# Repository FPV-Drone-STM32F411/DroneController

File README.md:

# FPV Drone PCB Full PCB + Code + Assembly

**A comprehensive, fully open-source FPV drone platform**: a two-board avionics stack (flight computer + power/ESC) complete with their codebase *and* a lightweight, robust airframe. All KiCad 9.0 design files, firmware, and CAD are included. Media of all PCBs, schematics and airframe are attached within this repository. 

## Overview

This project develops an FPV drone around two custom 5×5 PCBs: a **STM32F411 flight computer** and a **STM32F405 power distribution + ESC board**. esigned for compatibility with **Betaflight** (FC) and **AM32** (ESC). Both are built around the STM32 chipset and designed to be compatible with BetaFlight and AM32 requirements.

**Manufacturing Sponsor:** Huge thanks to **[PCBWay](https://www.pcbway.com/)** for sponsoring fabrication and assembly of the MKII flight computer. Their high-quality manufacturing, quick turnaround, significantly accelerated the build process. Moreover, their service was excellent and addressed questions promptly and clearly. As a bonus, PCBWay offers affordable, unique **silkscreen colours**. PCBWay is highly recommended and proved to be a great fit for the FPV-Drone-STM32F411 project.

**MKII Flight Computer 3D Model**

**What’s new (MKII & Airframe)**
- **MKII Flight Computer:** UART and SWD flash options, cost-efficient and compact IMU (ICM-42605), oscilloscope-friendly SPI test pads, expanded test points, JST connectors, improved routing for debugability.
- **Open-Source Airframe:** integrated landing legs, structural reinforcements, and geometry to accommodate **~935 KV BLDC motors**; CAD provided for easy printing/mods.

## Airframe

The airframe is designed to be **robust and lightweight** with:
- **Integrated landing legs** and **structural reinforcements** for durability  
- Geometry to suit **~935 KV** brushless motors (modeled in CAD)  
- CAD provided for printing and customization

**Printing tips (suggested):**
- Arms/plates: CF-reinforced nylon or strong PLA+/PETG  
- Landing legs: TPU for impact absorption
- Verify clearances for your chosen motor + prop combo (aimed at 5″ class)

## Hardware Details

 **Integrated PCB Design**
  - Flight Controller: STM32F411CEU6 (ARM Cortex M4)
  - Power/ESC Board: High-current paths, AM32 compatible design
    
 **Connectivity**
  - All peripherals utilize SPI for high-speed sensor communication
  - USB-C, JTAG, SWD
  - UART port for external peripheral
  - Backup Coin Cell Battery Port
  - FTDI programming interface

<ins>**Flight Controller Board**</ins>
- STM32F411CEU6 microcontroller
- 12MHz external crystal oscillator
- ICM-42605 gyroscope/accelerometer
- BMP280 barometer for altitude hold
- L86-M33 GPS for postional tracking
- SX 1276 LoRa 915MHz Transciever NiceRF Module
- Power options, USB-C, LDO and External 3.3V Connection

<ins>**Power and ESC Board**</ins>

**Power System**
- SWD Flash
- DC-DC buck converter for efficient power regulation
- Support for 3S-4S LiPo batteries (11.1V-16.8V)
- XT-60 connector for battery input
- Electric Speed Controller for a BLDC motor

**Electronic Speed Controller (ESC)**
- AM32 compatible
- 10A 935 KV motor capability
- Thermal management design

## Software Compatibility

This drone design is compatible with:
- BetaFlight (recommended for racing/freestyle)
- INAV (for GPS functions)
- Ardupilot (for autonomous capabilities)
- AM32 (for ESC functionality)
- STM32CUBEIDE (Coded in C for entire codebase)

### Bill of Materials

| Component | Description | Specification |
|-----------|-------------|---------------|
| Frame | Open-Source CAD | 5″ class geometry w/ landing legs   |
| Motors | Brushless | 935 KV (example: 1800 KV 5″ also viable) |
| Battery | LiPo | 4S 1500mAh 100C (recommended) |
| Propellers | 5-inch | Matched to motor and frame |
| Camera | FPV | CCD or CMOS based on preference |
| Video Transmitter | 5.8GHz | Power output based on needs |
| Receiver | Radio control | Compatible with SX1276 LoRa Transciever |
| LoRa Antenna | 915MHz |SMA compatible quarter-wavelength antenna|

### Electronics Knowledge
- Basic soldering skills
- Understanding of power systems
- Familiarity with microcontrollers
- Ability to flash firmware through CUBEIDE

## Testing Procedures

1. Power system verification (voltage output, regulation)
2. Motor/ESC testing with oscillosocpe
3. SPI testing using oscciloscope test pads
4. Sensor calibration and verification
5. Radio range and failsafe testing
6. Controlled hover tests
7. Full flight testing

# Media
## Most Updated
### Airframe

### MKII of Flight Computer 

**MKII Flight Computer 3D Model**

**MKII Flight Computer PCB**

\

**MKI Flight Computer Schematic**

**MKII Flight Computer Firmware Data Acquistion**

***Disclaimer: GPS outputs are example outputs***

### MKI of Electric Speed Controller 

**MKI of ESC 3D Model**

**MKI of ESC PCB**

**MKI of ESC Schematic**

## Historical
### MKI of Flight Computer
**MKI Flight Computer 3D Model**

**MKI Flight Computer PCB**

**MKI Flight Computer Schematic**

## Collaboration

This project is in collaboration with Ammar Mahmood and esb8, all PCB designs, CAD modelling, firmware modifications, and build documentation are developed jointly to ensure the highest quality and performance.

## License

This project is released under the MIT License. All design files, including schematics, PCB layouts, and firmware modifications are open source and available for personal and commercial use with attribution.

## Resources

- [PCBWay](https://www.pcbway.com/)
- [BetaFlight Documentation](https://betaflight.com/docs/getting-started/installation)
- [STM32F4 Reference Manual](https://www.st.com/resource/en/reference_manual/rm0383-stm32f411xce-advanced-armbased-32bit-mcus-stmicroelectronics.pdf)
- [ESB8 GitHub Repository](https://github.com/esb8)
- [Ammar Github Repository](https://github.com/ammarjmahmood)
- [Project GitHub Repository](https://github.com/your-username/esb8-fpv-drone)

---
*This FPV drone project aims to combine and create a full documentation on the latest in drone technology with custom-designed electronics to create a high-performance, reliable platform for racing, freestyle, or aerial photography.*

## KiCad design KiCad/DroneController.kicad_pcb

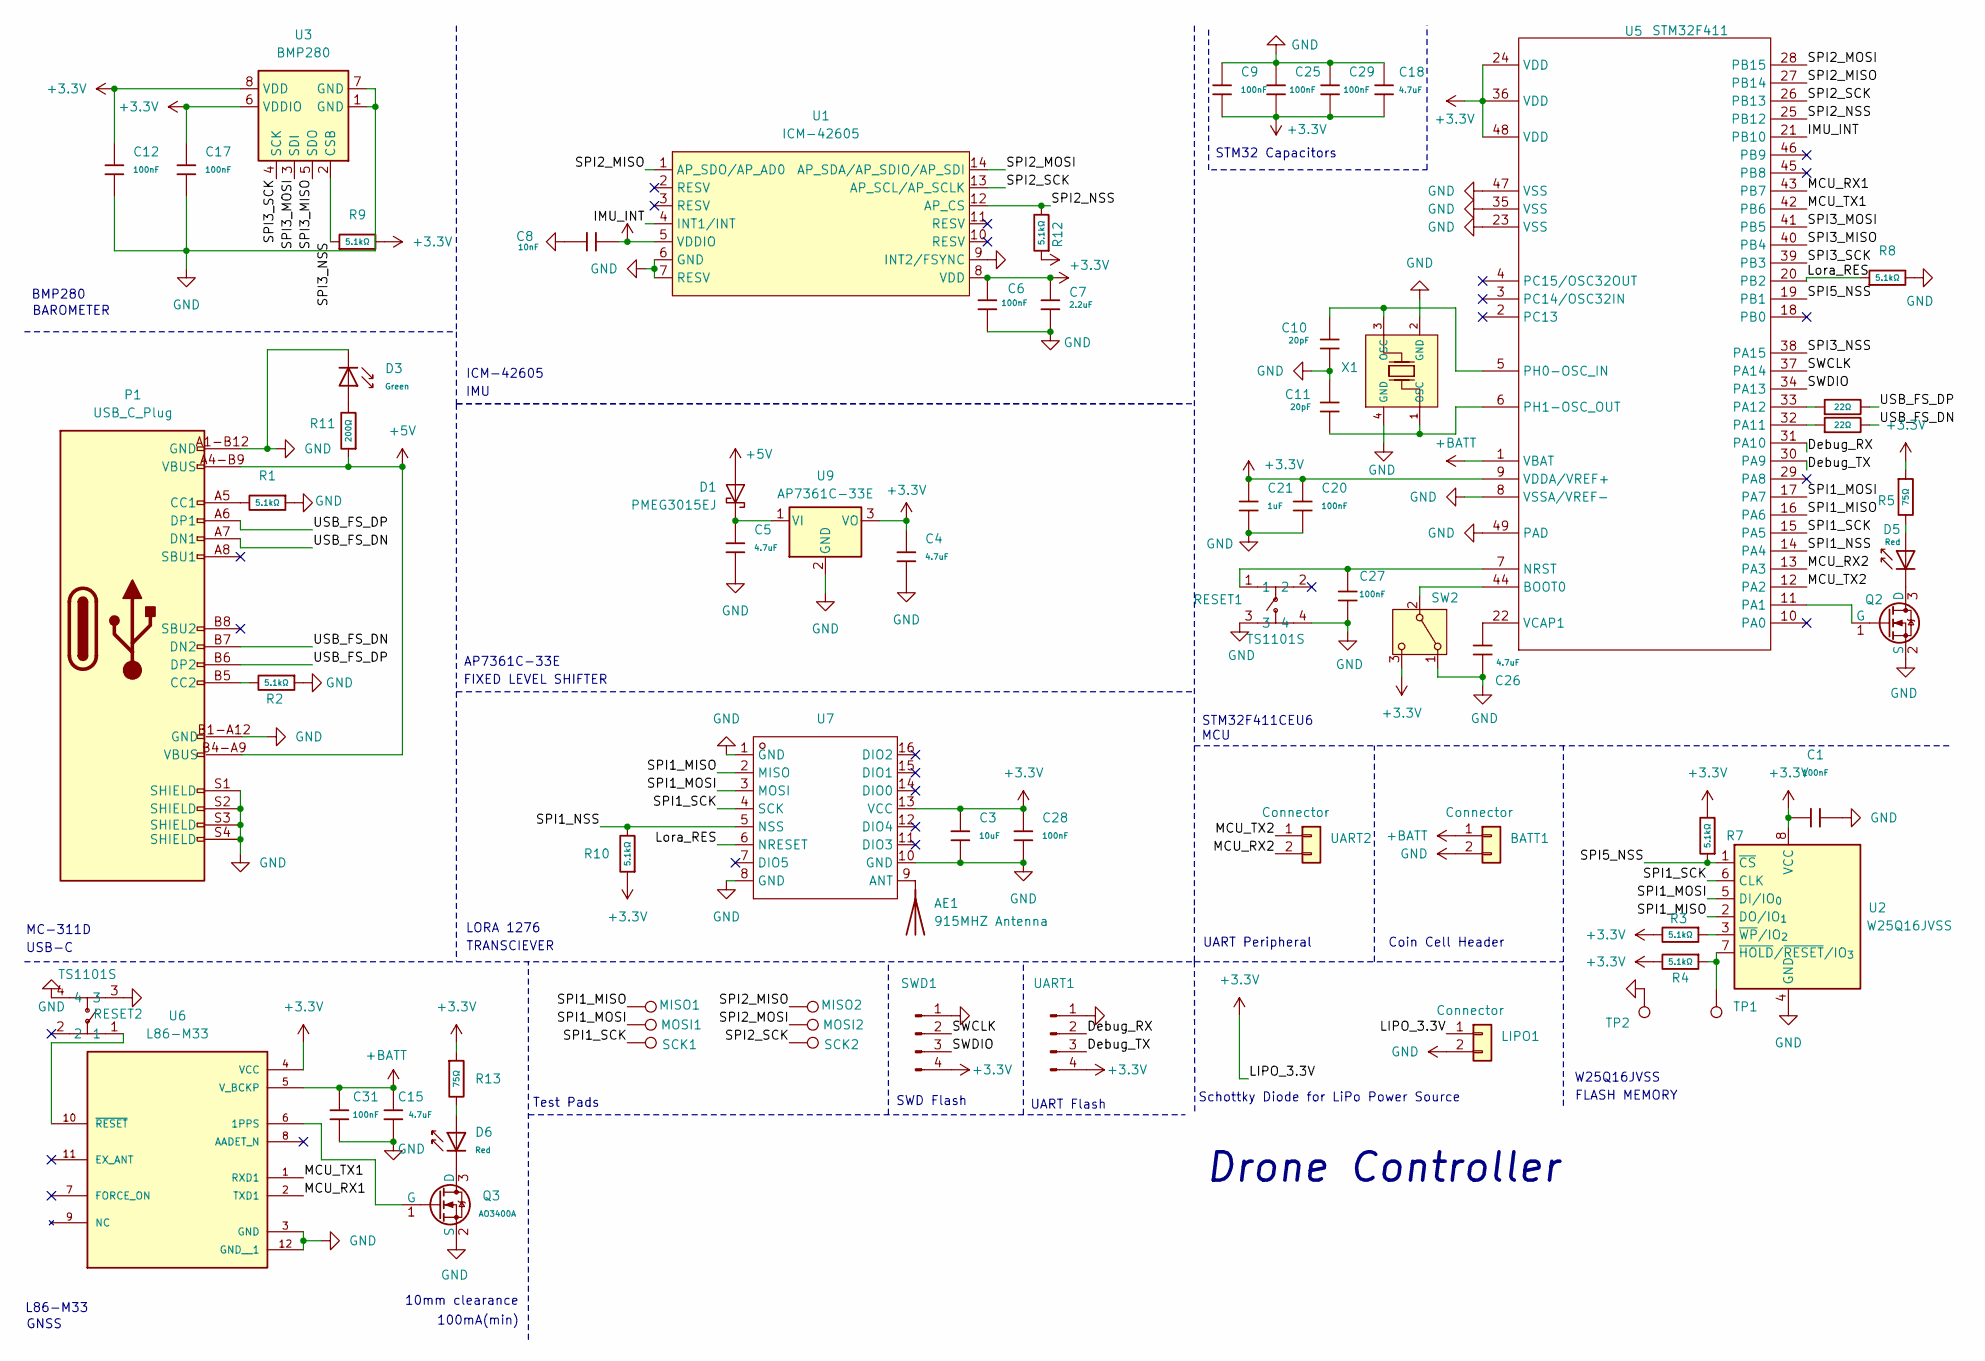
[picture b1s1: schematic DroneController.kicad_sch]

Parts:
AE1: 915MHZ Antenna; SMA_BAT_Wireless_BWSMA-KWE-Z001; LCSC Part Number C496551
BATT1: Connector; CONN-TH_B2B-XH-A-LF-SN; LCSC Part Number C158012
C1, C6, C9, C12, C17, C20, C25, C27, C28, C29, C31: 100nF; C_0402; Voltage Rated 16V; Tolerance ±10%; Part CL05B104KO5NNNC; LCSC Part Number C1525
C3: 10uF; C_0402; Voltage Rated 6.3V; Tolerance ±20%; Part CL05A106MQ5NUNC; LCSC C15525
C4, C5, C15, C18, C26: 4.7uF; C_0402; Voltage Rated 10V; Tolerance ±20%; Part CL05A475MP5NRNC; LCSC Part Number C23733
C7: 2.2uF; C_0402; Voltage Rated 10V; Tolerance ±10%; Part CL05A225MQ5NSNC; LCSC Part Number C2999759
C8: 10nF; C_0402; Voltage Rated 50V; Tolerance ±10%; Part CL05B103KB5NNNC; LCSC Part Number C15195
C10, C11: 20pF; C_0402; Voltage Rated 50V; Tolerance ±5%; Part 0402CG200J500NT; LCSC Part Number C1554
C21: 1uF; C_0402; Voltage Rated 25V; Tolerance ±10%; Part CL05A105KA5NQNC; LCSC Part Number C52923
D1: PMEG3015EJ; D_SOD-323F; LCSC Part Number C32798641
D3: Green; D_0805; Part KT-0805G; LCSC Part Number C2297
D5, D6: Red; D_0805; Forward Voltage (VF) 1.6V~2.6V; Part NCD0805R1; LCSC Part Number C84256
LIPO1: Connector; CONN-TH_B2B-XH-A-LF-SN; LCSC Part Number C158012
MISO1, MISO2: TestPoint; TestPoint_Keystone_5019_Miniature; LCSC Part Number C238131
MOSI1, MOSI2: TestPoint; TestPoint_Keystone_5019_Miniature; LCSC Part Number C238131
P1: USB_C_Plug; USB-C; LCSC Part Number C136423
Q2, Q3: AO3400A; Q_SOT-23; Part AO3400A; LCSC Part Number C20917
R1, R2, R3, R4, R7, R9, R10, R12: 5.1kΩ; R_0402; Overload Voltage (Max) 50V; Tolerance ±1%; Part 0402WGF5101TCE; LCSC Part Number C25905
R5, R13: 75Ω; R_0603; Overload Voltage (Max) 75V; Tolerance ±1%; Part 0603WAF750JT5E; LCSC Part Number C4275
R6, R14: 22Ω; R_0402; Overload Voltage (Max) 50V; Tolerance ±1%; Part 0402WGF220JTCE; LCSC Part Number C25092
R8: 5.1kΩ; R_0402; Overload Voltage (Max) 50V; Tolerance ±1%; Part 0402WGF5101TCE; LCSC C25905
R11: 200Ω; R_0402; Overload Voltage (Max) 50V; Tolerance ±1%; Part 0402WGF2000TCE; LCSC Part Number C25087
RESET1, RESET2: TS1101S; SW-SMD_4P-L4.5-W4.5-P3.15-LS7.5-TL; LCSC Part Number C49274267
SCK1, SCK2: TestPoint; TestPoint_Keystone_5019_Miniature; LCSC Part Number C238131
SW2: SW_SPDT; SW-SMD_SHOUHAN_MST-22D18G23J_C2875122; LCSC Part Number C2875122
SWD1: Conn_01x04_Pin; PinHeader_1x04_P2.00mm_Vertical; LCSC Part Number C541858
TP1, TP2: TestPoint
U1: ICM-42605; LGA-14_L3.0-W2.5-P0.50-TL; LCSC Part Number C2655099
U2: W25Q16JVSS; SOIC-8_5.3x5.3mm_P1.27mm; LCSC Part Number C131025
U3: BMP280; Bosch_LGA-8_2x2.5mm_P0.65mm_ClockwisePinNumbering; LCSC Part Number C83291
U5: STM32F411; QFN-48-1EP_7x7mm_P0.5mm_EP5.6x5.6mm; LCSC Part Number C60420
U6: L86-M33; XCVR_L86-M33; Digikey Part Number 2958-L86-M33CT-ND
U7: 915MHz; COMM-SMD_LORA1276-C1-915MHZ; LCSC Part Number C3001531
U9: AP7361C-33E; SOT-223-3_TabPin2; LCSC Part Number C500795
UART1: Conn_01x04_Pin; PinHeader_1x04_P2.00mm_Vertical; LCSC Part Number C541858
UART2: Connector; CONN-TH_B2B-XH-A-LF-SN; LCSC Part Number C158012
X1: Shenzhen SCTF Elec SX2B12.000F1010F30; Crystal_SMD_2520-4Pin_2.5x2.0mm; Frequency Tolerance ±10ppm; Part X322512MSB4SI; LCSC Part Number C7301971

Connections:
+3.3V: C1.2, C3.1, C4.1, C6.2, C7.1, C8.2, C9.2, C12.1, C17.1, C18.1, C20.1, C21.1, C25.2, C28.1, C29.2, LIPO1.1, R3.2, R4.2, R5.1, R7.2, R9.2, R10.1, R12.1, R13.1, SW2.3 (C), SWD1.4, U1.5 (VDDIO), U1.8 (VDD), U2.8 (VCC), U3.6 (VDDIO), U3.8 (VDD), U5.9 (VDDA/VREF+), U5.24 (VDD), U5.36 (VDD), U5.48 (VDD), U6.4 (VCC), U7.13 (VCC), U9.3 (VO), UART1.4; also elsewhere on the board
+5V: D1.2 (A), P1.A4-B9 (VBUS), P1.B4-A9 (VBUS), R11.1
+BATT: BATT1.1, C15.1, C31.1, U5.1 (VBAT), U6.5 (V_BCKP)
/Debug_RX: U5.31 (PA10), UART1.2
/Debug_TX: U5.30 (PA9), UART1.3
/IMU_INT: U1.4 (INT1/INT), U5.21 (PB10)
/Lora_RES: R8.1, U5.20 (PB2), U7.6 (NRESET)
/MCU_RX1: U5.43 (PB7), U6.2 (TXD1)
/MCU_RX2: U5.13 (PA3), UART2.2
/MCU_TX1: U5.42 (PB6), U6.1 (RXD1)
/MCU_TX2: U5.12 (PA2), UART2.1
/SPI1_MISO: MISO1.1, U2.2 (DO/IO_{1}), U5.16 (PA6), U7.2 (MISO)
/SPI1_MOSI: MOSI1.1, U2.5 (DI/IO_{0}), U5.17 (PA7), U7.3 (MOSI)
/SPI1_NSS: R10.2, U5.14 (PA4), U7.5 (NSS)
/SPI1_SCK: SCK1.1, U2.6 (CLK), U5.15 (PA5), U7.4 (SCK)
/SPI2_MISO: MISO2.1, U1.1 (AP_SDO/AP_AD0), U5.27 (PB14)
/SPI2_MOSI: MOSI2.1, U1.14 (AP_SDA/AP_SDIO/AP_SDI), U5.28 (PB15)
/SPI2_NSS: R12.2, U1.12 (AP_CS), U5.25 (PB12)
/SPI2_SCK: SCK2.1, U1.13 (AP_SCL/AP_SCLK), U5.26 (PB13)
/SPI3_MISO: U3.5 (SDO), U5.40 (PB4)
/SPI3_MOSI: U3.3 (SDI), U5.41 (PB5)
/SPI3_NSS: R9.1, U3.2 (CSB), U5.38 (PA15)
/SPI3_SCK: U3.4 (SCK), U5.39 (PB3)
/SPI5_NSS: R7.1, U2.1 (~CS), U5.19 (PB1)
/SWCLK: SWD1.2, U5.37 (PA14)
/SWDIO: SWD1.3, U5.34 (PA13)
/USB_FS_DN: P1.A7 (DN1), P1.B7 (DN2), R6.2
/USB_FS_DP: P1.A6 (DP1), P1.B6 (DP2), R14.2
GND: BATT1.2, C1.1, C3.2, C4.2, C5.2, C6.1, C7.2, C8.1, C9.1, C10.2, C11.1, C12.2, C15.2, C17.2, C18.2, C20.2, C21.2, C25.1, C26.2, C27.2, C28.2, C29.1, C31.2, D3.1, LIPO1.2, P1.A1-B12 (GND), P1.B1-A12 (GND), P1.S1 (SHIELD), P1.S2 (SHIELD), P1.S3 (SHIELD), P1.S4 (SHIELD), Q2.2 (S), Q3.2 (S), R1.1, R2.1, R8.2, RESET1.3, RESET1.4, RESET2.3, RESET2.4, SW2.1 (A), SWD1.1, TP2.1, U1.6 (GND), U1.7 (RESV), U1.9 (INT2/FSYNC), U2.4 (GND), U3.1 (GND), U3.7 (GND), U5.8 (VSSA/VREF-), U5.23 (VSS), U5.35 (VSS), U5.47 (VSS), U5.49 (PAD), U6.3 (GND), U6.12 (GND__1), U7.1 (GND), U7.8 (GND), U7.10 (GND), U9.2 (GND), UART1.1, X1.2 (GND), X1.4 (GND); also elsewhere on the board
unnamed: AE1.1 (A), U7.9 (ANT)
unnamed: C5.1, D1.1 (K), U9.1 (VI)
unnamed: D3.2, R11.2
unnamed: D5.2, R5.2
unnamed: D6.2, R13.2
unnamed: P1.A5 (CC1), R1.2
unnamed: P1.B5 (CC2), R2.2
unnamed: D5.1, Q2.3 (D)
unnamed: Q2.1 (G), U5.11 (PA1)
unnamed: D6.1, Q3.3 (D)
unnamed: Q3.1 (G), U6.6 (1PPS)
unnamed: SW2.2 (B), U5.44 (BOOT0)
unnamed: R4.1, TP1.1, U2.7 (~HOLD/~RESET/IO_{3})
unnamed: R3.1, U2.3 (~WP/IO_{2})
unnamed: C27.1, RESET1.1, U5.7 (NRST)
unnamed: R6.1, U5.32 (PA11)
unnamed: R14.1, U5.33 (PA12)
unnamed: C10.1, U5.5 (PH0-OSC_IN), X1.3 (OSC)
unnamed: C11.2, U5.6 (PH1-OSC_OUT), X1.1 (OSC)
unnamed: C26.1, U5.22 (VCAP1)
unnamed: RESET2.1, U6.10 (~RESET)

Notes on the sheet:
TRANSCIEVER
FLASH MEMORY
STM32F411CEU6
Drone Controller
ICM-42605
UART Peripheral
Coin Cell Header
L86-M33
Schottky Diode for LiPo Power Source
Test Pads
IMU
MC-311D
SWD Flash
UART Flash
100mA(min)
AP7361C-33E
FIXED LEVEL SHIFTER
BAROMETER
USB-C
10mm clearance
BMP280
STM32 Capacitors
GNSS
MCU
W25Q16JVSS
LORA 1276

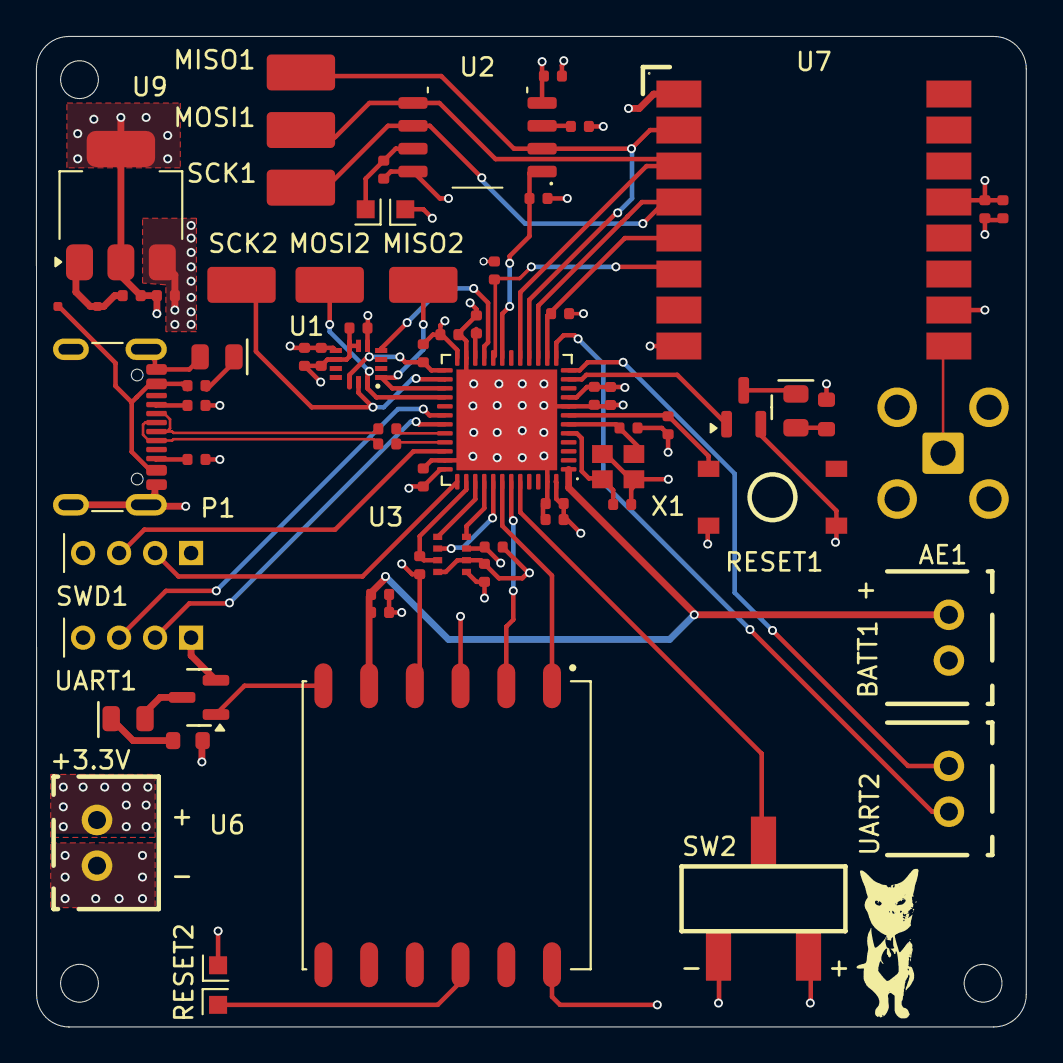
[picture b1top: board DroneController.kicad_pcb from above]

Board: 4 copper layers, 55.0 x 55.0 mm, 65 parts (0 on the bottom side), 49 nets.

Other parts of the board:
+3.3V: Connector; CONN-TH_B2B-XH-A-LF-SN

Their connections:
+3.3V: +3.3V.2; also elsewhere on the board
GND: +3.3V.1; also elsewhere on the board

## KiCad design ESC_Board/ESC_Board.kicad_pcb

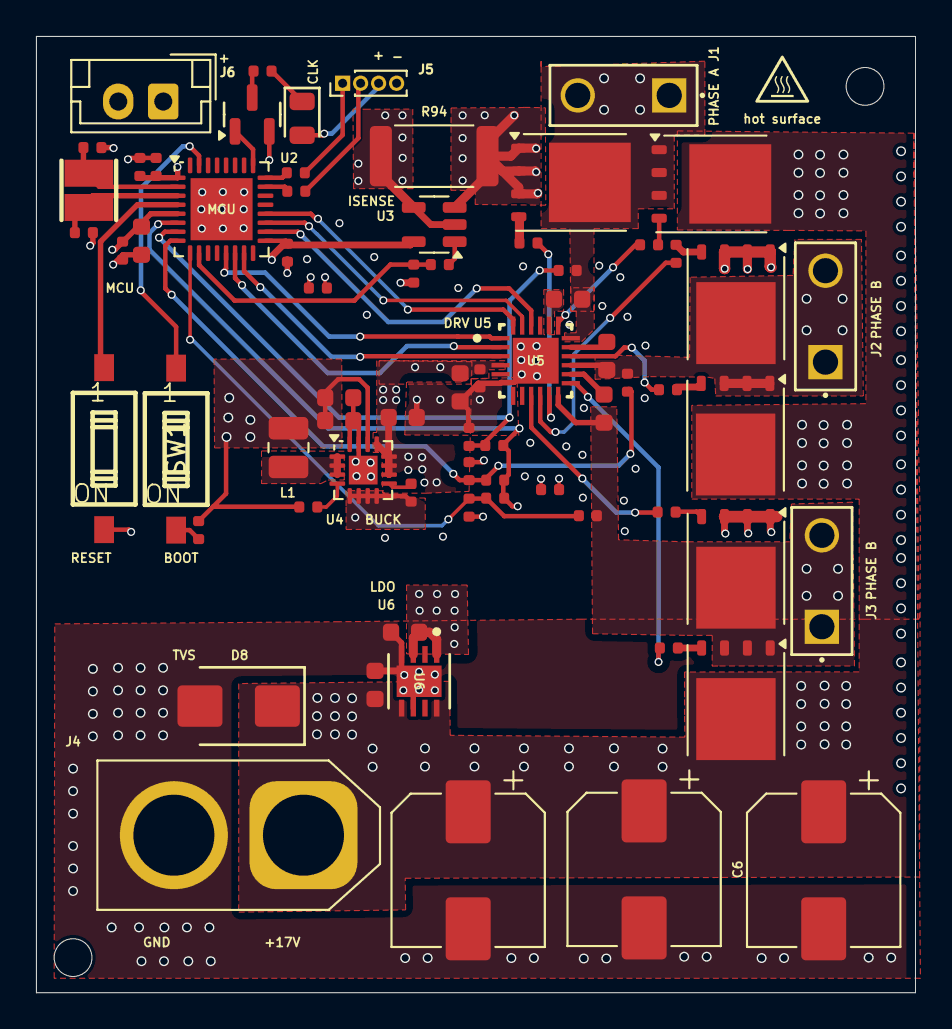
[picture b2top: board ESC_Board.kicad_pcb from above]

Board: 4 copper layers, 48.8 x 53.1 mm, 70 parts (0 on the bottom side), 50 nets.

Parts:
C1, C7, C9, C16, C56, C58: 100nF; C_0402
C5, C6, C8: 100uF; CP_Elec_8x10
C10: 4.7uF; C_0402
C11, C15, C21, C53, C54: 10uF; C_0603
C12: 10nF; C_0402
C13: 3.3nF; C_0402
C20, C23, C24, C25, C26: 1uF; C_0603
C52, C55: 22pF; C_0402
D1: Red; D_0805
D8: SMBJ18A; D_SMB
J1, J2, J3: 63824-1; TRM2_63824-1_TEC
J4: Conn_01x02_Pin; AMASS_XT60-F_1x02_P7.20mm_Vertical
J5: Conn_01x04_Pin; PinHeader_1x04_P1.00mm_Vertical
J6: Conn_01x02_Pin; JST_EH_B2B-EH-A_1x02_P2.50mm_Vertical
L1: L; L_1008_2520Metric
Q1: AO3400A; Q_SOT-23
Q3, Q4, Q5, Q7, Q8: SIR182DP; TDSON-8-1
Q6: SIR182Dp; TDSON-8-1
R1, R5: 100Ω; R_0402
R2, R13, R23, R26: 1kΩ; R_0402
R3: 75Ω; R_0402
R7: 100kΩ; R_0402
R11, R14, R21, R22, R24, R25, R27: 10kΩ; R_0402
R15, R16, R17, R18, R19, R20: 22Ω; R_0402
R94: 3.0m; R_2512_6332Metric
SW1, SW2: SW_SPST; SW-SMD_2P-L3.5-W6.2-P2.54-LS9.8
U2: STM32F051K8Ux; QFN-32-1EP_5x5mm_P0.5mm_EP3.45x3.45mm
U3: INA180A1; SOT-23-5
U4: TPS62153RGTT; TQFN-16-1EP_3x3mm_P0.5mm_EP1.6x1.6mm
U5: DRV8300DRGER; RGE0024B-IPC_A
U6: TLV76601QWDRBRQ1; DRB0008J-IPC_A
Y1: Crystal_Small; OSC-SMD_2P-L3.2-W2.5

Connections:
+3.3V: C7.1, C9.1, C10.1, C12.1, C26.1, C53.2, C54.2, C56.1, D1.2, J5.3, J6.1, L1.2, R7.2, R11.1, U2.1 (VDD), U2.5 (VDDA), U2.17 (VDD), U3.5 (V+), U4.14 (VOS)
+12V: C11.1, C15.2, C16.1, C21.1, C58.1, U4.10 (AVIN), U4.11 (PVIN), U4.12 (PVIN__1), U4.13 (EN), U5.4 (GVDD), U6.1 (OUT), U6.3 (SNS)
+17V: C5.1, C6.1, C8.1, C20.1, D8.1, J4.1, Q5.5 (D), Q6.5 (D), Q7.5 (D), U6.5 (EN), U6.8 (IN)
/BEMFA: R13.1, R14.2, R21.1, U2.7 (PA1)
/BEMFB: R22.2, R23.1, R24.1, U2.8 (PA2)
/BEMFC: R25.2, R26.1, R27.1, U2.9 (PA3)
/BEMFCOMMON: R14.1, R22.1, R25.1, U2.6 (PA0)
/GHA: R15.1, U5.19 (GHA)
/GHB: R17.1, U5.16 (GHB)
/GHC: R19.1, U5.13 (GHC)
/GLA: R16.1, U5.11 (GLA)
/GLB: R18.1, U5.10 (GLB)
/GLC: R20.1, U5.9 (GLC)
/INHA: U2.18 (PA8), U5.22 (INHA)
/INHB: U2.19 (PA9), U5.23 (INHB)
/INHC: U2.20 (PA10), U5.24 (INHC)
/INLA: U2.13 (PA7), U5.1 (INLA)
/INLB: U2.14 (PB0), U5.2 (INLB)
/INLC: U2.15 (PB1), U5.3 (INLC)
/I_SENSE: C1.1, R2.2, U2.10 (PA4)
/LOW_COMMON: Q3.1 (S), Q3.2 (S), Q3.3 (S), Q4.1 (S), Q4.2 (S), Q4.3 (S), Q8.1 (S), Q8.2 (S), Q8.3 (S), R94.1, U3.3 (+)
/MOTORA: C23.2, J1.1, J1.2, Q3.5 (D), Q5.1 (S), Q5.2 (S), Q5.3 (S), R21.2, U5.18 (SHA)
/MOTORB: C24.2, J2.1, J2.2, Q4.5 (D), Q6.1 (S), Q6.2 (S), Q6.3 (S), R24.2, U5.15 (SHB)
/MOTORC: C25.2, J3.1, J3.2, Q7.1 (S), Q7.2 (S), Q7.3 (S), Q8.5 (D), R27.2, U5.12 (SHC)
/SWCLK: J5.1, R5.2
/SWDIO: J5.2, R1.2
GND: C1.2, C5.2, C6.2, C7.2, C8.2, C9.2, C10.2, C11.2, C12.2, C13.1, C15.1, C16.2, C20.2, C21.2, C26.2, C52.2, C53.1, C54.1, C55.2, C56.2, C58.2, D8.2, J4.2, J5.4, J6.2, Q1.2 (S), R13.2, R23.2, R26.2, R94.2, SW1.2 (B), U2.33 (VSS), U3.2 (GND), U3.4 (-), U4.5 (FB), U4.6 (AGND), U4.7 (FSW), U4.8 (DEF), U4.15 (PGND), U4.16 (PGND__1), U4.17 (EP), U5.6 (GND), U5.25 (PowerPAD), U6.4 (GND), U6.6 (GND), U6.9 (Thermal_Pad)
unnamed: D1.1, R3.2
unnamed: Q1.3 (D), R3.1
unnamed: Q1.1 (G), U2.25 (PA15)
unnamed: Q3.4 (G), R16.2
unnamed: Q4.4 (G), R18.2
unnamed: Q5.4 (G), R15.2
unnamed: Q6.4 (G), R17.2
unnamed: Q7.4 (G), R19.2
unnamed: Q8.4 (G), R20.2
unnamed: R2.1, U3.1
unnamed: SW1.1 (A), U2.4 (NRST)
unnamed: SW2.1 (A), U2.31 (BOOT0)
unnamed: R11.2, SW2.2 (B)
unnamed: R1.1, U2.23 (PA13)
unnamed: R5.1, U2.24 (PA14)
unnamed: C55.1, U2.2 (PF0), Y1.1
unnamed: C52.1, U2.3 (PF1), Y1.2
unnamed: R7.1, U4.4 (PG)
unnamed: C13.2, U4.9 (SS-TR)
unnamed: L1.1, U4.1 (SW), U4.2 (SW__1), U4.3 (SW__2)
unnamed: C23.1, U5.20 (BSTA)
unnamed: C24.1, U5.17 (BSTB)
unnamed: C25.1, U5.14 (BSTC)

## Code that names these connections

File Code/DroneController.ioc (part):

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Mcu.Name=STM32F411C(C-E)Ux
Mcu.Package=UFQFPN48
Mcu.UserName=STM32F411CEUx
PA1.GPIOParameters=GPIO_Label
PA1.GPIO_Label=LED
PA1.Signal=GPIO_Output
PA11.Mode=Device_Only
PA11.Signal=USB_OTG_FS_DM
PA12.Mode=Device_Only
PA12.Signal=USB_OTG_FS_DP
PA13.Mode=Serial_Wire
PA13.Signal=SYS_JTMS-SWDIO
PA14.Mode=Serial_Wire
PA14.Signal=SYS_JTCK-SWCLK
PA15.GPIOParameters=GPIO_Label
PA15.GPIO_Label=NSS3
PA15.Signal=GPIO_Output
PA2.Mode=Asynchronous
PA2.Signal=USART2_TX
PA3.Mode=Asynchronous
PA3.Signal=USART2_RX
PA4.GPIOParameters=GPIO_Label
PA4.GPIO_Label=NSS1
PA4.Signal=GPIO_Output
PA5.Mode=Full_Duplex_Master
PA5.Signal=SPI1_SCK
PA6.Mode=Full_Duplex_Master
PA6.Signal=SPI1_MISO
PA7.Mode=Full_Duplex_Master
PA7.Signal=SPI1_MOSI
PB1.GPIOParameters=GPIO_Label
PB1.GPIO_Label=NSS5
PB1.Signal=GPIO_Output
PB12.GPIOParameters=GPIO_Label
PB12.GPIO_Label=NSS2
PB12.Signal=GPIO_Output
PB13.Mode=Full_Duplex_Master
PB13.Signal=SPI2_SCK
PB14.Mode=Full_Duplex_Master
PB14.Signal=SPI2_MISO
PB15.Mode=Full_Duplex_Master
PB15.Signal=SPI2_MOSI
PB3.Mode=Full_Duplex_Master
PB3.Signal=SPI3_SCK
PB4.Mode=Full_Duplex_Master
PB4.Signal=SPI3_MISO
PB5.Mode=Full_Duplex_Master
PB5.Signal=SPI3_MOSI
PB6.Mode=Asynchronous
PB6.Signal=USART1_TX
PB7.Mode=Asynchronous
PB7.Signal=USART1_RX
PH0\ -\ OSC_IN.Mode=HSE-External-Oscillator
PH0\ -\ OSC_IN.Signal=RCC_OSC_IN
PH1\ -\ OSC_OUT.Mode=HSE-External-Oscillator
PH1\ -\ OSC_OUT.Signal=RCC_OSC_OUT
RCC.HSE_VALUE=12000000
RCC.SYSCLKFreq_VALUE=72000000
RCC.SYSCLKSource=RCC_SYSCLKSOURCE_PLLCLK
board=custom

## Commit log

2025-07-22 Modified BMP280 wiring, cleaned up schematic
2025-08-07 ESC Board: Major overhauls to schematic, preliminary layout
2025-08-07 Finalized Layout for ESC Board
2025-08-07 Update README.md
    Updated README with media of the completed ESC Board and the Flight Computer Board.
2025-08-09 Optimized Signal Integrity, added stichting vias, and stiching capacitors between PWR and GND layers
2025-09-02 Added Codebase, Reorganized file directory to support added code
2025-09-02 fixed repo
2025-09-04 Added working code for IMU and Barometer, displaying acceleration,gyro, pitch, yaw, temperature, altitude, pressure
2025-09-08 Changed ESC Board Connector to XT30-M from XT30-F
2025-09-08 Added working code for IMU, Barometer, SX1276, W25 Flash Memory
2026-02-08 Added CAD models for PCB and Drone
